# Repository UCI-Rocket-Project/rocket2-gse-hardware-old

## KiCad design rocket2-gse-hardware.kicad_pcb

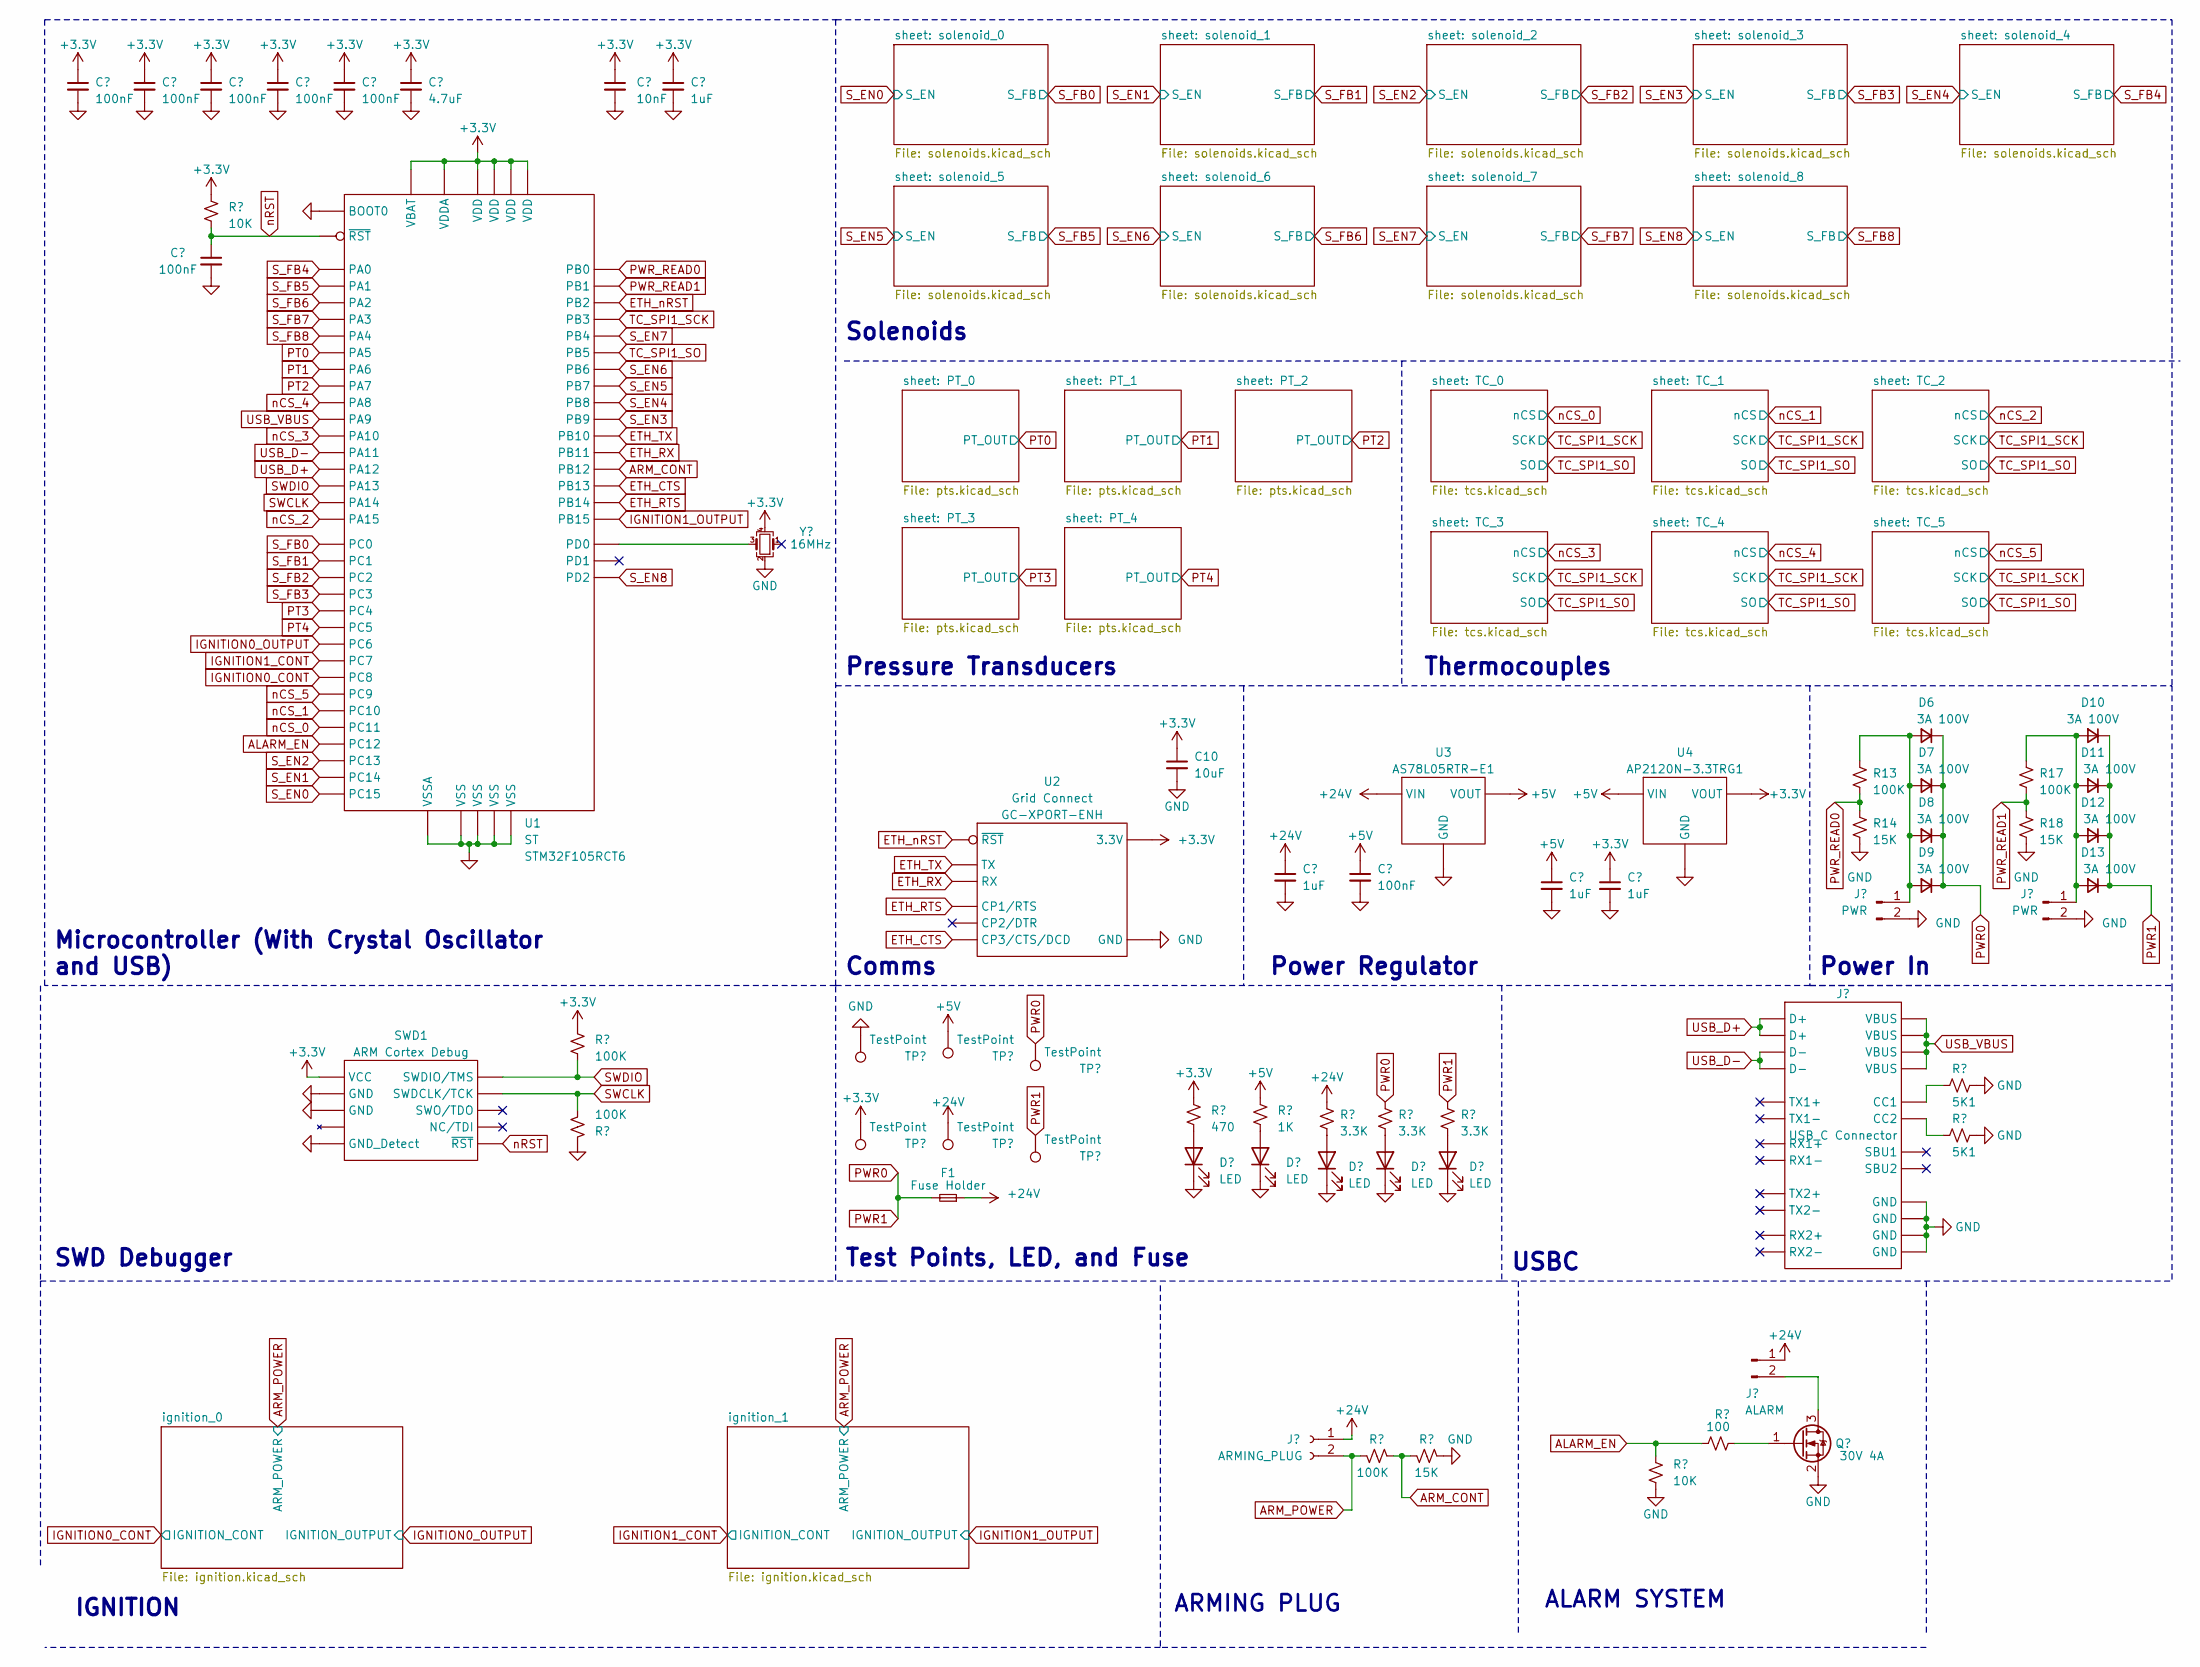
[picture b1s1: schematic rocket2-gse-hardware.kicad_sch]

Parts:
C1, C2, C3, C4, C5, C6, C12: 100nF; C_0402_1005Metric; Part # Generic 100nF 0402 Capacitor
C7: 4.7uF; C_0402_1005Metric; Part # Generic 4.7uF 0402 Capacitor
C8: 10nF; C_0402_1005Metric; Part # Generic 10nF 0402 Capacitor
C9, C11, C13, C14: 1uF; C_0402_1005Metric; Part # Generic 1uF 0402 Capacitor
C10: 10uF; C_0402_1005Metric; Part # Generic 10uF 0402 Capacitor
D1, D2, D3, D4, D5: LED; LED_0603_1608Metric; Part # Generic 0603 Red LED
D6, D7, D8, D9, D10, D11, D12, D13: 3A 100V; D_SMA; Part # SL310A-TP
F1: Fuse Holder; Fuseholder_Blade_Mini_Keystone_3568; Part # 3568-15
J1: ARMING_PLUG; TerminalBlock_bornier-2_P5.08mm
J2: ALARM; TerminalBlock_bornier-2_P5.08mm
J3: USB_C Connector; USB_C_Receptacle_GCT_USB4105-xx-A_16P_TopMnt_Horizontal; Part # 629105150521
J4, J5: PWR; BarrelJack_Horizontal
Q1: 30V 4A; SOT-23-3; Part # DMG3402L
R1, R11: 10K; R_0402_1005Metric; Part # Generic 10K 1% 0402 Resistor
R2, R3, R7, R13, R17: 100K; R_0402_1005Metric; Part # Generic 100K 1% 0402 Resistor
R4: 470; R_0402_1005Metric; Part # Generic 470 1% 0402 Resistor
R5: 1K; R_0402_1005Metric; Part # Generic 1K 1% 0402 Resistor
R6, R8, R10: 3.3K; R_0402_1005Metric; Part # Generic 3.3K 1% 0402 Resistor
R9, R14, R18: 15K; R_0402_1005Metric; Part # Generic 15K 1% 0402 Resistor
R12: 100; R_0402_1005Metric; Part # Generic 100 1% 0402 Resistor
R15, R16: 5K1; R_0402_1005Metric; Part # Generic 5K1 1% 0402 Resistor
SWD1: ARM Cortex Debug; PinHeader_2x05_P1.27mm_Vertical_SMD; Part # Generic 2x5 1.27mm Connector
TP1, TP2, TP3, TP4, TP5, TP6: TestPoint; TestPoint_Pad_D2.0mm
U1: LQFP-64_10x10mm_P0.5mm; Part # STM32F105RCT6
U2: GC-XPORT; Part # GC-XPORT-ENH
U3: SOT-89-3; Part # AS78L05RTR-E1
U4: SOT-23-3; Part # AP2120N-3.3TRG1
Y1: 16MHz; Crystal_SMD_2016-4Pin_2.0x1.6mm; Part # ECS-1633-160-BN-TR

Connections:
+3.3V: C1.1, C2.1, C3.1, C5.1, C6.1, C7.1, C8.1, C9.1, C10.1, C14.1, R1.1, R2.1, R4.2, SWD1.1 (VCC), TP2.1, U1.1 (VBAT), U1.13 (VDDA), U1.19 (VDD), U1.32 (VDD), U1.48 (VDD), U1.64 (VDD), U2.2 (3.3V), U4.2 (VOUT), Y1.4; also elsewhere on the board
+5V: C12.1, C13.1, R5.2, TP3.1, U3.1 (VOUT), U4.3 (VIN); also elsewhere on the board
+24V: C11.1, F1.1, J1.1, J2.1, R10.2, TP4.1, U3.3 (VIN); also elsewhere on the board
ALARM_EN: R11.1, R12.1, U1.53 (PC12)
ARM_CONT: R7.2, R9.1, U1.33 (PB12)
ARM_POWER: J1.2, R7.1; also elsewhere on the board
ETH_CTS: U1.34 (PB13), U2.8 (CP3/CTS/DCD)
ETH_RTS: U1.35 (PB14), U2.6 (CP1/RTS)
ETH_RX: U1.30 (PB11), U2.5 (RX)
ETH_TX: U1.29 (PB10), U2.4 (TX)
ETH_nRST: U1.28 (PB2), U2.3 (~RST)
GND: C1.2, C2.2, C3.2, C4.2, C5.2, C6.2, C7.2, C8.2, C9.2, C10.2, C11.2, C12.2, C13.2, C14.2, D1.1 (K), D2.1 (K), D3.1 (K), D4.1 (K), D5.1 (K), J3.A1 (GND), J3.A12 (GND), J3.B1 (GND), J3.B12 (GND), J4.2, J5.2, Q1.2 (S), R3.1, R9.2, R11.2, R14.2, R15.1, R16.1, R18.2, SWD1.3 (GND), SWD1.5 (GND), SWD1.9 (GND_Detect), TP1.1, U1.12 (VSSA), U1.18 (VSS), U1.31 (VSS), U1.47 (VSS), U1.60 (BOOT0), U1.63 (VSS), U2.1 (GND), U3.2 (GND), U4.1 (GND), Y1.2; also elsewhere on the board
IGNITION0_CONT: U1.39 (PC8); also elsewhere on the board
IGNITION0_OUTPUT: U1.37 (PC6); also elsewhere on the board
IGNITION1_CONT: U1.38 (PC7); also elsewhere on the board
IGNITION1_OUTPUT: U1.36 (PB15); also elsewhere on the board
unnamed: D1.2 (A), R4.1
unnamed: D2.2 (A), R5.1
unnamed: D3.2 (A), R10.1
unnamed: D4.2 (A), R6.1
unnamed: D5.2 (A), R8.1
unnamed: D6.2 (A), D7.2 (A), D8.2 (A), D9.2 (A), J4.1, R13.1
unnamed: D10.2 (A), D11.2 (A), D12.2 (A), D13.2 (A), J5.1, R17.1
unnamed: J2.2, Q1.3 (D)
unnamed: J3.A5 (CC1), R15.2
unnamed: J3.B5 (CC2), R16.2
unnamed: Q1.1 (G), R12.2
unnamed: U1.5 (PD0), Y1.3
PT0: U1.21 (PA5); also elsewhere on the board
PT1: U1.22 (PA6); also elsewhere on the board
PT2: U1.23 (PA7); also elsewhere on the board
PT3: U1.24 (PC4); also elsewhere on the board
PT4: U1.25 (PC5); also elsewhere on the board
PWR0: D6.1 (K), D7.1 (K), D8.1 (K), D9.1 (K), D10.1 (K), D11.1 (K), D12.1 (K), D13.1 (K), F1.2, R6.2, R8.2, TP5.1, TP6.1
PWR_READ0: R13.2, R14.1, U1.26 (PB0)
PWR_READ1: R17.2, R18.1, U1.27 (PB1)
SWCLK: R3.2, SWD1.4 (SWDCLK/TCK), U1.49 (PA14)
SWDIO: R2.2, SWD1.2 (SWDIO/TMS), U1.46 (PA13)
S_EN0: U1.4 (PC15); also elsewhere on the board
S_EN1: U1.3 (PC14); also elsewhere on the board
S_EN2: U1.2 (PC13); also elsewhere on the board
S_EN3: U1.62 (PB9); also elsewhere on the board
S_EN4: U1.61 (PB8); also elsewhere on the board
S_EN5: U1.59 (PB7); also elsewhere on the board
S_EN6: U1.58 (PB6); also elsewhere on the board
S_EN7: U1.56 (PB4); also elsewhere on the board
S_EN8: U1.54 (PD2); also elsewhere on the board
S_FB0: U1.8 (PC0); also elsewhere on the board
S_FB1: U1.9 (PC1); also elsewhere on the board
S_FB2: U1.10 (PC2); also elsewhere on the board
S_FB3: U1.11 (PC3); also elsewhere on the board
S_FB4: U1.14 (PA0); also elsewhere on the board
S_FB5: U1.15 (PA1); also elsewhere on the board
S_FB6: U1.16 (PA2); also elsewhere on the board
S_FB7: U1.17 (PA3); also elsewhere on the board
S_FB8: U1.20 (PA4); also elsewhere on the board
TC_SPI1_SCK: U1.55 (PB3); also elsewhere on the board
TC_SPI1_SO: U1.57 (PB5); also elsewhere on the board
USB_D+: J3.A6 (D+), J3.B6 (D+), U1.45 (PA12)
USB_D-: J3.A7 (D-), J3.B7 (D-), U1.44 (PA11)
USB_VBUS: J3.A4 (VBUS), J3.A9 (VBUS), J3.B4 (VBUS), J3.B9 (VBUS), U1.42 (PA9)
nCS_0: U1.52 (PC11); also elsewhere on the board
nCS_1: U1.51 (PC10); also elsewhere on the board
nCS_2: U1.50 (PA15); also elsewhere on the board
nCS_3: U1.43 (PA10); also elsewhere on the board
nCS_4: U1.41 (PA8); also elsewhere on the board
nCS_5: U1.40 (PC9); also elsewhere on the board
nRST: C4.1, R1.2, SWD1.10 (~RST), U1.7 (~RST)

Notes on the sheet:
ARMING PLUG
ALARM SYSTEM
Thermocouples
Comms
SWD Debugger
Test Points, LED, and Fuse
Pressure Transducers
Microcontroller (With Crystal Oscillator and USB)
Power In
Power Regulator
IGNITION
USBC
Solenoids

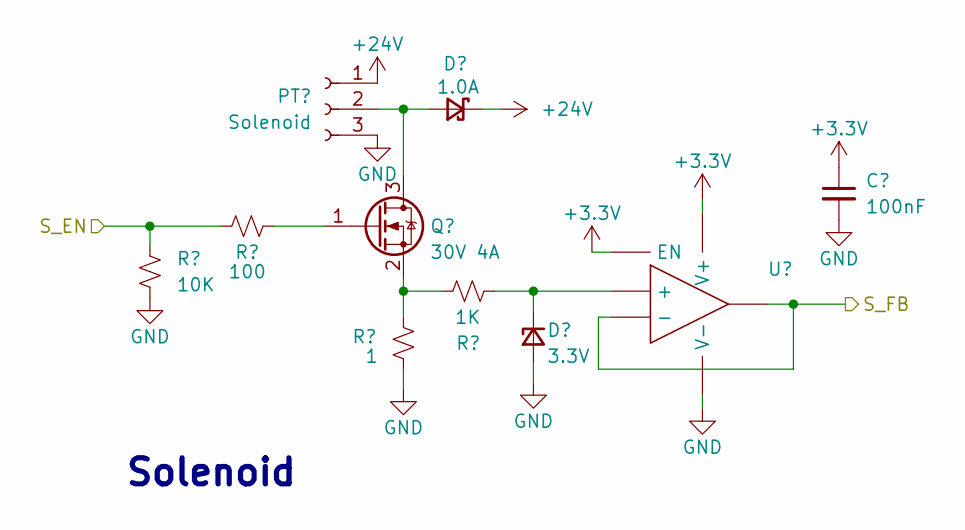
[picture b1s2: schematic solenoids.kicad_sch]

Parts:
C15: 100nF; C_0402_1005Metric; Part # Generic 100nF 0402 Capacitor
D14: 1.0A; D_SMA; Part # S1M
D15: 3.3V; D_SOD-123; Part # MMSZ4684T1G
Q2: 30V 4A; SOT-23-3; Part # DMG3402L
R19: 10K; R_0402_1005Metric; Part # Generic 10K 1% 0402 Resistor
R20: 100; R_0402_1005Metric; Part # Generic 100 1% 0402 Resistor
R21: 1; R_1206_3216Metric; Part # Generic 1 1% 1206 Resistor
R22: 1K; R_0402_1005Metric; Part # Generic 1K 1% 0402 Resistor
S0: Solenoid; TerminalBlock_bornier-3_P5.08mm
U5: SOT-23-6; Part # OPA357AIDBVT

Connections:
+3.3V: C15.1, U5.5 (EN), U5.6 (V+); also elsewhere on the board
+24V: D14.1 (K), S0.1; also elsewhere on the board
GND: C15.2, D15.2 (A), R19.2, R21.2, S0.3, U5.2 (V-); also elsewhere on the board
unnamed: D14.2 (A), Q2.3 (D), S0.2
unnamed: D15.1 (K), R22.2, U5.3 (+)
unnamed: Q2.1 (G), R20.2
unnamed: Q2.2 (S), R21.1, R22.1
S_EN0: R19.1, R20.1; also elsewhere on the board
S_FB0: U5.1, U5.4 (-); also elsewhere on the board

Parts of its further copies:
C16, C17, C18, C19, C20, C21, C22, C23: 100nF; C_0402_1005Metric; Part # Generic 100nF 0402 Capacitor
D16, D18, D20, D22, D24, D26, D28, D30: 1.0A; D_SMA; Part # S1M
D17, D19, D21, D23, D25, D27, D29, D31: 3.3V; D_SOD-123; Part # MMSZ4684T1G
Q3, Q4, Q5, Q6, Q7, Q8, Q9, Q10: 30V 4A; SOT-23-3; Part # DMG3402L
R23, R27, R31, R35, R39, R43, R47, R51: 10K; R_0402_1005Metric; Part # Generic 10K 1% 0402 Resistor
R24, R28, R32, R36, R40, R44, R48, R52: 100; R_0402_1005Metric; Part # Generic 100 1% 0402 Resistor
R25, R29, R33, R37, R41, R45, R49, R53: 1; R_1206_3216Metric; Part # Generic 1 1% 1206 Resistor
R26, R30, R34, R38, R42, R46, R50, R54: 1K; R_0402_1005Metric; Part # Generic 1K 1% 0402 Resistor
S1, S2, S3, S4, S5, S6, S7, S8: Solenoid; TerminalBlock_bornier-3_P5.08mm
U6, U7, U8, U9, U10, U11, U12, U13: SOT-23-6; Part # OPA357AIDBVT

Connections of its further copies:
+3.3V: C16.1, C17.1, C18.1, C19.1, C20.1, C21.1, C22.1, C23.1, U6.5 (EN), U6.6 (V+), U7.5 (EN), U7.6 (V+), U8.5 (EN), U8.6 (V+), U9.5 (EN), U9.6 (V+), U10.5 (EN), U10.6 (V+), U11.5 (EN), U11.6 (V+), U12.5 (EN), U12.6 (V+), U13.5 (EN), U13.6 (V+); also elsewhere on the board
+24V: D16.1 (K), D18.1 (K), D20.1 (K), D22.1 (K), D24.1 (K), D26.1 (K), D28.1 (K), D30.1 (K), S1.1, S2.1, S3.1, S4.1, S5.1, S6.1, S7.1, S8.1; also elsewhere on the board
GND: C16.2, C17.2, C18.2, C19.2, C20.2, C21.2, C22.2, C23.2, D17.2 (A), D19.2 (A), D21.2 (A), D23.2 (A), D25.2 (A), D27.2 (A), D29.2 (A), D31.2 (A), R23.2, R25.2, R27.2, R29.2, R31.2, R33.2, R35.2, R37.2, R39.2, R41.2, R43.2, R45.2, R47.2, R49.2, R51.2, R53.2, S1.3, S2.3, S3.3, S4.3, S5.3, S6.3, S7.3, S8.3, U6.2 (V-), U7.2 (V-), U8.2 (V-), U9.2 (V-), U10.2 (V-), U11.2 (V-), U12.2 (V-), U13.2 (V-); also elsewhere on the board
unnamed: D16.2 (A), Q3.3 (D), S1.2
unnamed: D17.1 (K), R26.2, U6.3 (+)
unnamed: D18.2 (A), Q4.3 (D), S2.2
unnamed: D19.1 (K), R30.2, U7.3 (+)
unnamed: D20.2 (A), Q5.3 (D), S3.2
unnamed: D21.1 (K), R34.2, U8.3 (+)
unnamed: D22.2 (A), Q6.3 (D), S4.2
unnamed: D23.1 (K), R38.2, U9.3 (+)
unnamed: D24.2 (A), Q7.3 (D), S5.2
unnamed: D25.1 (K), R42.2, U10.3 (+)
unnamed: D26.2 (A), Q8.3 (D), S6.2
unnamed: D27.1 (K), R46.2, U11.3 (+)
unnamed: D28.2 (A), Q9.3 (D), S7.2
unnamed: D29.1 (K), R50.2, U12.3 (+)
unnamed: D30.2 (A), Q10.3 (D), S8.2
unnamed: D31.1 (K), R54.2, U13.3 (+)
unnamed: Q3.1 (G), R24.2
unnamed: Q3.2 (S), R25.1, R26.1
unnamed: Q4.1 (G), R28.2
unnamed: Q4.2 (S), R29.1, R30.1
unnamed: Q5.1 (G), R32.2
unnamed: Q5.2 (S), R33.1, R34.1
unnamed: Q6.1 (G), R36.2
unnamed: Q6.2 (S), R37.1, R38.1
unnamed: Q7.1 (G), R40.2
unnamed: Q7.2 (S), R41.1, R42.1
unnamed: Q8.1 (G), R44.2
unnamed: Q8.2 (S), R45.1, R46.1
unnamed: Q9.1 (G), R48.2
unnamed: Q9.2 (S), R49.1, R50.1
unnamed: Q10.1 (G), R52.2
unnamed: Q10.2 (S), R53.1, R54.1
S_EN1: R23.1, R24.1; also elsewhere on the board
S_EN2: R27.1, R28.1; also elsewhere on the board
S_EN3: R31.1, R32.1; also elsewhere on the board
S_EN4: R35.1, R36.1; also elsewhere on the board
S_EN5: R39.1, R40.1; also elsewhere on the board
S_EN6: R43.1, R44.1; also elsewhere on the board
S_EN7: R47.1, R48.1; also elsewhere on the board
S_EN8: R51.1, R52.1; also elsewhere on the board
S_FB1: U6.1, U6.4 (-); also elsewhere on the board
S_FB2: U7.1, U7.4 (-); also elsewhere on the board
S_FB3: U8.1, U8.4 (-); also elsewhere on the board
S_FB4: U9.1, U9.4 (-); also elsewhere on the board
S_FB5: U10.1, U10.4 (-); also elsewhere on the board
S_FB6: U11.1, U11.4 (-); also elsewhere on the board
S_FB7: U12.1, U12.4 (-); also elsewhere on the board
S_FB8: U13.1, U13.4 (-); also elsewhere on the board

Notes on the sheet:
Solenoid

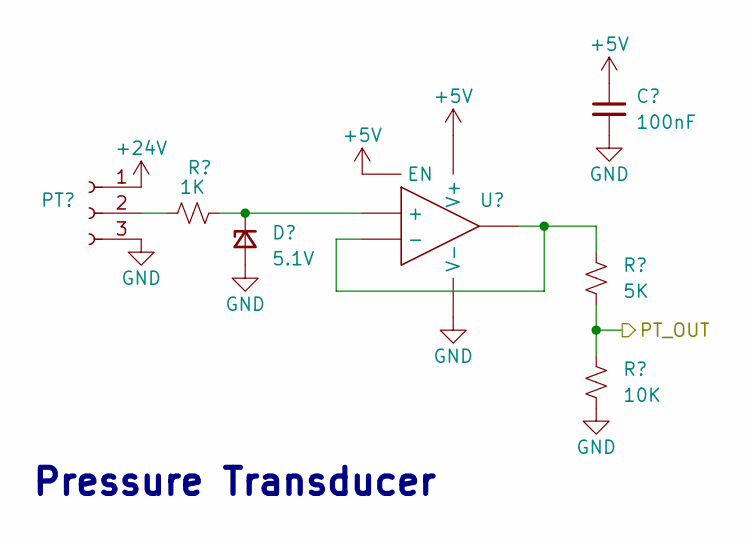
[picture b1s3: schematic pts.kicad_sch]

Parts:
C27: 100nF; C_0402_1005Metric; Part # Generic 100nF 0402 Capacitor
D35: 5.1V; D_MiniMELF; Part # BZV55-B5V1,115
PT2: Pressure Transducer 1; TerminalBlock_bornier-3_P5.08mm
R64: 1K; R_0402_1005Metric; Part # Generic 1K 1% 0402 Resistor
R65: 5K; R_0402_1005Metric; Part # Generic 5K 1% 0402 Resistor
R66: 10K; R_0402_1005Metric; Part # Generic 10K 1% 0402 Resistor
U17: SOT-23-6; Part # OPA357AIDBVT

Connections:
+5V: C27.1, U17.5 (EN), U17.6 (V+); also elsewhere on the board
+24V: PT2.1; also elsewhere on the board
GND: C27.2, D35.2 (A), PT2.3, R66.2, U17.2 (V-); also elsewhere on the board
unnamed: D35.1 (K), R64.2, U17.3 (+)
unnamed: PT2.2, R64.1
unnamed: R65.1, U17.1, U17.4 (-)
PT2: R65.2, R66.1; also elsewhere on the board

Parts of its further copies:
C24, C25, C26, C28: 100nF; C_0402_1005Metric; Part # Generic 100nF 0402 Capacitor
D32, D33, D34, D36: 5.1V; D_MiniMELF; Part # BZV55-B5V1,115
PT0, PT1, PT3, PT4: Pressure Transducer 1; TerminalBlock_bornier-3_P5.08mm
R55, R58, R61, R67: 1K; R_0402_1005Metric; Part # Generic 1K 1% 0402 Resistor
R56, R59, R62, R68: 5K; R_0402_1005Metric; Part # Generic 5K 1% 0402 Resistor
R57, R60, R63, R69: 10K; R_0402_1005Metric; Part # Generic 10K 1% 0402 Resistor
U14, U15, U16, U18: SOT-23-6; Part # OPA357AIDBVT

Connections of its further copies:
+5V: C24.1, C25.1, C26.1, C28.1, U14.5 (EN), U14.6 (V+), U15.5 (EN), U15.6 (V+), U16.5 (EN), U16.6 (V+), U18.5 (EN), U18.6 (V+); also elsewhere on the board
+24V: PT0.1, PT1.1, PT3.1, PT4.1; also elsewhere on the board
GND: C24.2, C25.2, C26.2, C28.2, D32.2 (A), D33.2 (A), D34.2 (A), D36.2 (A), PT0.3, PT1.3, PT3.3, PT4.3, R57.2, R60.2, R63.2, R69.2, U14.2 (V-), U15.2 (V-), U16.2 (V-), U18.2 (V-); also elsewhere on the board
unnamed: D32.1 (K), R55.2, U14.3 (+)
unnamed: D33.1 (K), R58.2, U15.3 (+)
unnamed: D34.1 (K), R61.2, U16.3 (+)
unnamed: D36.1 (K), R67.2, U18.3 (+)
unnamed: PT0.2, R61.1
unnamed: PT1.2, R58.1
unnamed: PT3.2, R67.1
unnamed: PT4.2, R55.1
unnamed: R56.1, U14.1, U14.4 (-)
unnamed: R59.1, U15.1, U15.4 (-)
unnamed: R62.1, U16.1, U16.4 (-)
unnamed: R68.1, U18.1, U18.4 (-)
PT0: R62.2, R63.1; also elsewhere on the board
PT1: R59.2, R60.1; also elsewhere on the board
PT3: R68.2, R69.1; also elsewhere on the board
PT4: R56.2, R57.1; also elsewhere on the board

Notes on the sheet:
Pressure Transducer

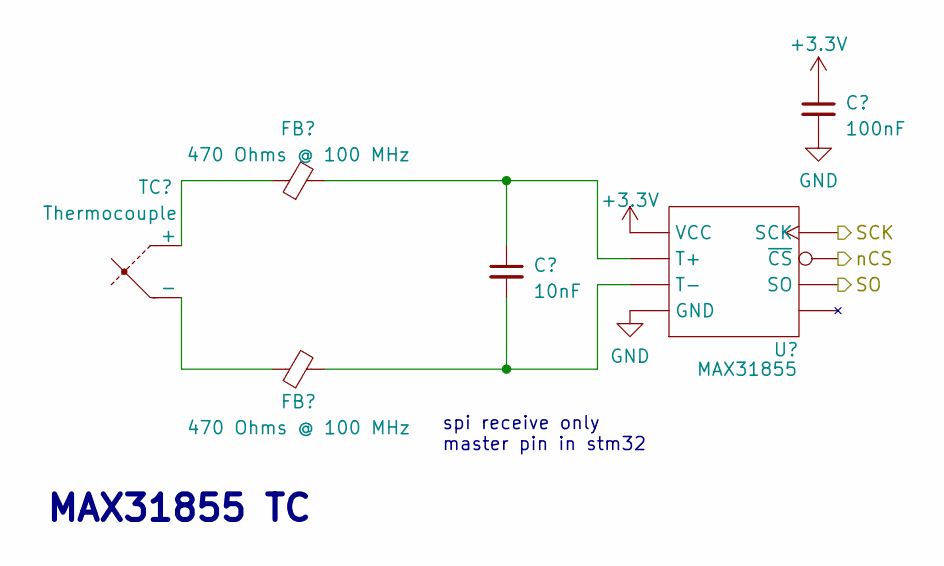
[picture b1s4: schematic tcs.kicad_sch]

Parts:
C39: 10nF; C_0402_1005Metric; Part # Generic 10nF 0402 Capacitor
C40: 100nF; C_0402_1005Metric; Part # Generic 100nF 0402 Capacitor
FB11, FB12: 470 Ohms @ 100 MHz; L_0603_1608Metric; Part # BLM18PG471SH1D
TC5: Thermocouple; AM-K-PCB; Part # AM-K-PCB
U24: SOIC-8_3.9x4.9mm_P1.27mm; Part # MAX31855

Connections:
+3.3V: C40.1, U24.4 (VCC); also elsewhere on the board
GND: C40.2, U24.1 (GND); also elsewhere on the board
unnamed: FB11.1, TC5.1 (+)
unnamed: FB12.1, TC5.2 (-)
unnamed: C39.1, FB11.2, U24.3 (T+)
unnamed: C39.2, FB12.2, U24.2 (T-)
TC_SPI1_SCK: U24.5 (SCK); also elsewhere on the board
TC_SPI1_SO: U24.7 (SO); also elsewhere on the board
nCS_5: U24.6 (~CS); also elsewhere on the board

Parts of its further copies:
C29, C31, C33, C35, C37: 10nF; C_0402_1005Metric; Part # Generic 10nF 0402 Capacitor
C30, C32, C34, C36, C38: 100nF; C_0402_1005Metric; Part # Generic 100nF 0402 Capacitor
FB1, FB2, FB3, FB4, FB5, FB6, FB7, FB8, FB9, FB10: 470 Ohms @ 100 MHz; L_0603_1608Metric; Part # BLM18PG471SH1D
TC0, TC1, TC2, TC3, TC4: Thermocouple; AM-K-PCB; Part # AM-K-PCB
U19, U20, U21, U22, U23: SOIC-8_3.9x4.9mm_P1.27mm; Part # MAX31855

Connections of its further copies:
+3.3V: C30.1, C32.1, C34.1, C36.1, C38.1, U19.4 (VCC), U20.4 (VCC), U21.4 (VCC), U22.4 (VCC), U23.4 (VCC); also elsewhere on the board
GND: C30.2, C32.2, C34.2, C36.2, C38.2, U19.1 (GND), U20.1 (GND), U21.1 (GND), U22.1 (GND), U23.1 (GND); also elsewhere on the board
unnamed: FB3.1, TC0.1 (+)
unnamed: FB4.1, TC0.2 (-)
unnamed: FB1.1, TC1.1 (+)
unnamed: FB2.1, TC1.2 (-)
unnamed: FB5.1, TC2.1 (+)
unnamed: FB6.1, TC2.2 (-)
unnamed: FB7.1, TC3.1 (+)
unnamed: FB8.1, TC3.2 (-)
unnamed: FB9.1, TC4.1 (+)
unnamed: FB10.1, TC4.2 (-)
unnamed: C29.1, FB1.2, U19.3 (T+)
unnamed: C29.2, FB2.2, U19.2 (T-)
unnamed: C31.1, FB3.2, U20.3 (T+)
unnamed: C31.2, FB4.2, U20.2 (T-)
unnamed: C33.1, FB5.2, U21.3 (T+)
unnamed: C33.2, FB6.2, U21.2 (T-)
unnamed: C35.1, FB7.2, U22.3 (T+)
unnamed: C35.2, FB8.2, U22.2 (T-)
unnamed: C37.1, FB9.2, U23.3 (T+)
unnamed: C37.2, FB10.2, U23.2 (T-)
TC_SPI1_SCK: U19.5 (SCK), U20.5 (SCK), U21.5 (SCK), U22.5 (SCK), U23.5 (SCK); also elsewhere on the board
TC_SPI1_SO: U19.7 (SO), U20.7 (SO), U21.7 (SO), U22.7 (SO), U23.7 (SO); also elsewhere on the board
nCS_0: U20.6 (~CS); also elsewhere on the board
nCS_1: U19.6 (~CS); also elsewhere on the board
nCS_2: U21.6 (~CS); also elsewhere on the board
nCS_3: U22.6 (~CS); also elsewhere on the board
nCS_4: U23.6 (~CS); also elsewhere on the board

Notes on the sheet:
spi receive only master pin in stm32
MAX31855 TC

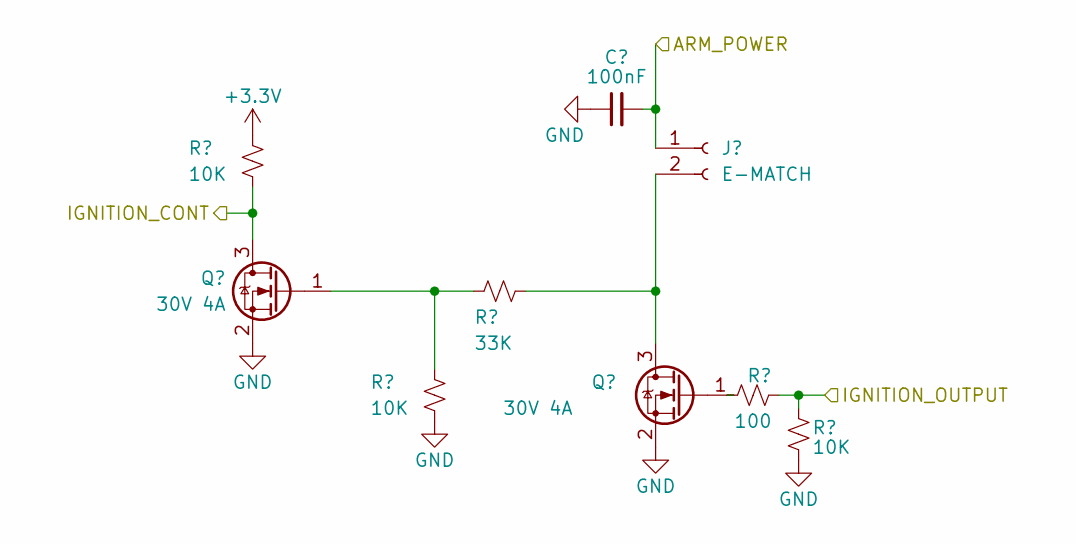
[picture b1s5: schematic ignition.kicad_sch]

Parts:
C42: 100nF; C_0402_1005Metric; Part # Generic 100nF 0402 Capacitor
J7: E-MATCH; TerminalBlock_bornier-2_P5.08mm
Q13, Q14: 30V 4A; SOT-23-3; Part # DMG3402L
R75, R76, R79: 10K; R_0402_1005Metric; Part # Generic 10K 1% 0402 Resistor
R77: 33K; R_0402_1005Metric; Part # Generic 33K 1% 0402 Resistor
R78: 100; R_0402_1005Metric; Part # Generic 100 1% 0402 Resistor

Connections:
+3.3V: R75.1; also elsewhere on the board
ARM_POWER: C42.2, J7.1; also elsewhere on the board
GND: C42.1, Q13.2 (S), Q14.2 (S), R76.2, R79.2; also elsewhere on the board
IGNITION0_CONT: Q13.3 (D), R75.2; also elsewhere on the board
IGNITION0_OUTPUT: R78.2, R79.1; also elsewhere on the board
unnamed: J7.2, Q14.3 (D), R77.1
unnamed: Q13.1 (G), R76.1, R77.2
unnamed: Q14.1 (G), R78.1

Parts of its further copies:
C41: 100nF; C_0402_1005Metric; Part # Generic 100nF 0402 Capacitor
J6: E-MATCH; TerminalBlock_bornier-2_P5.08mm
Q11, Q12: 30V 4A; SOT-23-3; Part # DMG3402L
R70, R71, R74: 10K; R_0402_1005Metric; Part # Generic 10K 1% 0402 Resistor
R72: 33K; R_0402_1005Metric; Part # Generic 33K 1% 0402 Resistor
R73: 100; R_0402_1005Metric; Part # Generic 100 1% 0402 Resistor

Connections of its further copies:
+3.3V: R70.1; also elsewhere on the board
ARM_POWER: C41.2, J6.1; also elsewhere on the board
GND: C41.1, Q11.2 (S), Q12.2 (S), R71.2, R74.2; also elsewhere on the board
IGNITION1_CONT: Q11.3 (D), R70.2; also elsewhere on the board
IGNITION1_OUTPUT: R73.2, R74.1; also elsewhere on the board
unnamed: J6.2, Q12.3 (D), R72.1
unnamed: Q11.1 (G), R71.1, R72.2
unnamed: Q12.1 (G), R73.1

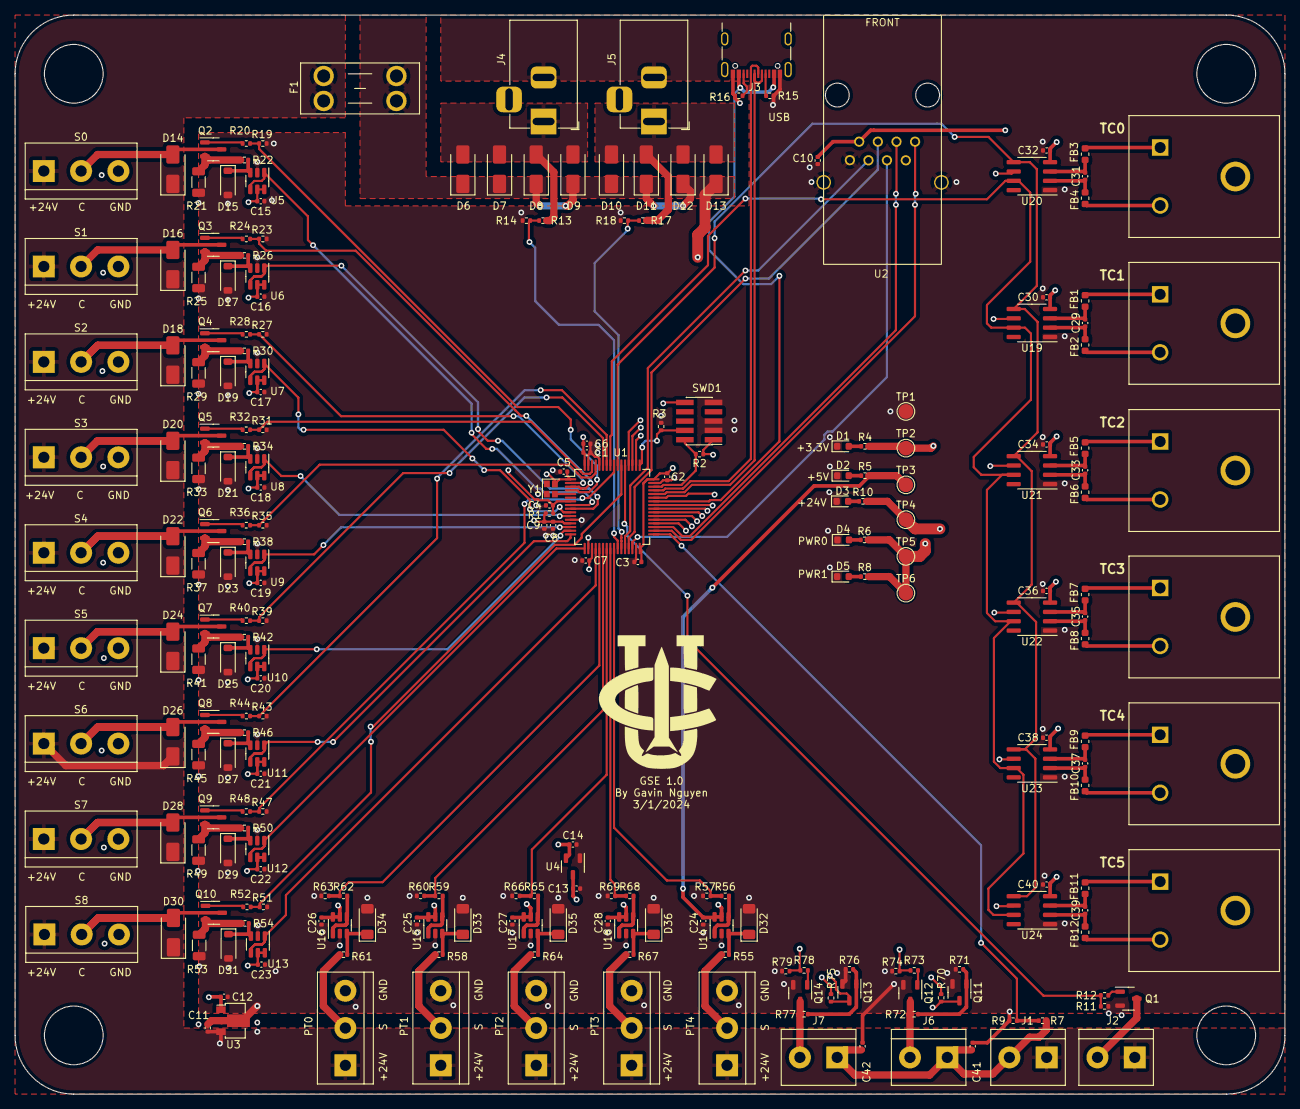
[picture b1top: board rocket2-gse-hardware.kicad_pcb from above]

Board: 4 copper layers, 173.0 x 147.0 mm, 243 parts (0 on the bottom side), 149 nets.

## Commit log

2024-02-09 added schematic and usbc
2024-02-10 fixed resistor values
2024-02-25 added full schematic and outdated pcb
2024-02-26 final polished schematic b4 daniel fixes nmosfet and ignition circuit
2024-02-28 Added in dual power, fuse, status led, and comments
2024-02-28 storing old schematic in commit before pulling
2024-03-02 finished pcb design of gse 1.0
2024-03-02 removed some thermal errors
2024-03-02 Fix planes
2024-03-03 fixed planes
2024-03-03 finished power planes
